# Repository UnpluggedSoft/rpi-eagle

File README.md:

# rpi-eagle
Eagle drawings for Raspberry Pi.

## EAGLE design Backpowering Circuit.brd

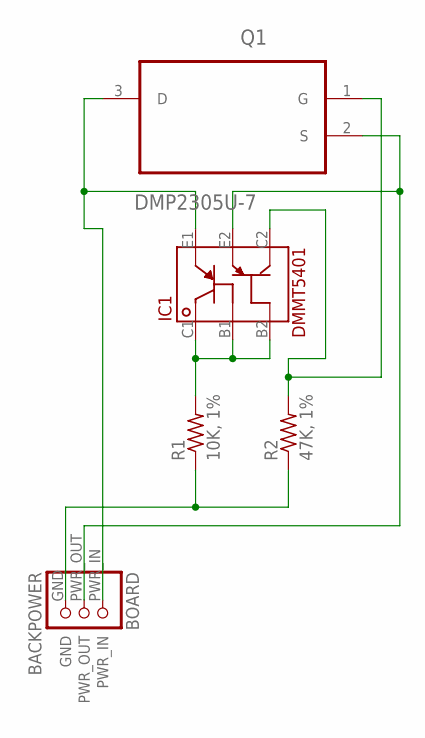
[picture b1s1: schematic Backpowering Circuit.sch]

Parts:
BOARD: BACKPOWER
IC1: DMMT5401
Q1: DMP2305U-7; SOT103P240X110-3N
R1: 10K, 1%; R1005
R2: 47K, 1%; R1005

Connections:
IN: BOARD.PWR_IN, IC1.E1, Q1.3 (D)
unnamed: BOARD.GND, R1.1, R2.1
unnamed: IC1.B1, IC1.B2, IC1.C1, R1.2
unnamed: IC1.C2, Q1.1 (G), R2.2
OUT: BOARD.PWR_OUT, IC1.E2, Q1.2 (S)

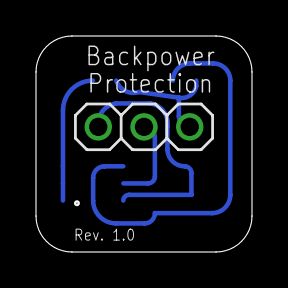
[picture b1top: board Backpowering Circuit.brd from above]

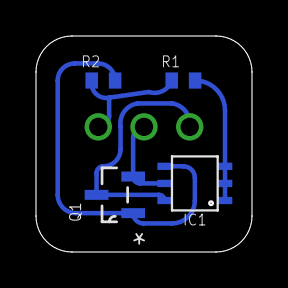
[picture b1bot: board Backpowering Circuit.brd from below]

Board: 2 copper layers, 12.0 x 12.0 mm, 5 parts (4 on the bottom side), 5 nets.

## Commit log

2015-09-22 Added Backpowering Circuit
2015-09-23 Convertd Backpowering Circuit schematic into a pluggable board.
2015-09-23 Added LICENSE.md.
    Exported library for Backpowering Circuit.
2015-10-02 Removed unneeded script.
